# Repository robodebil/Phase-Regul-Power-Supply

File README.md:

# Phase-Regul-Power-Supply
Выпускная Квалификационная работа. Лабораторный блок питания на фазовом управлении

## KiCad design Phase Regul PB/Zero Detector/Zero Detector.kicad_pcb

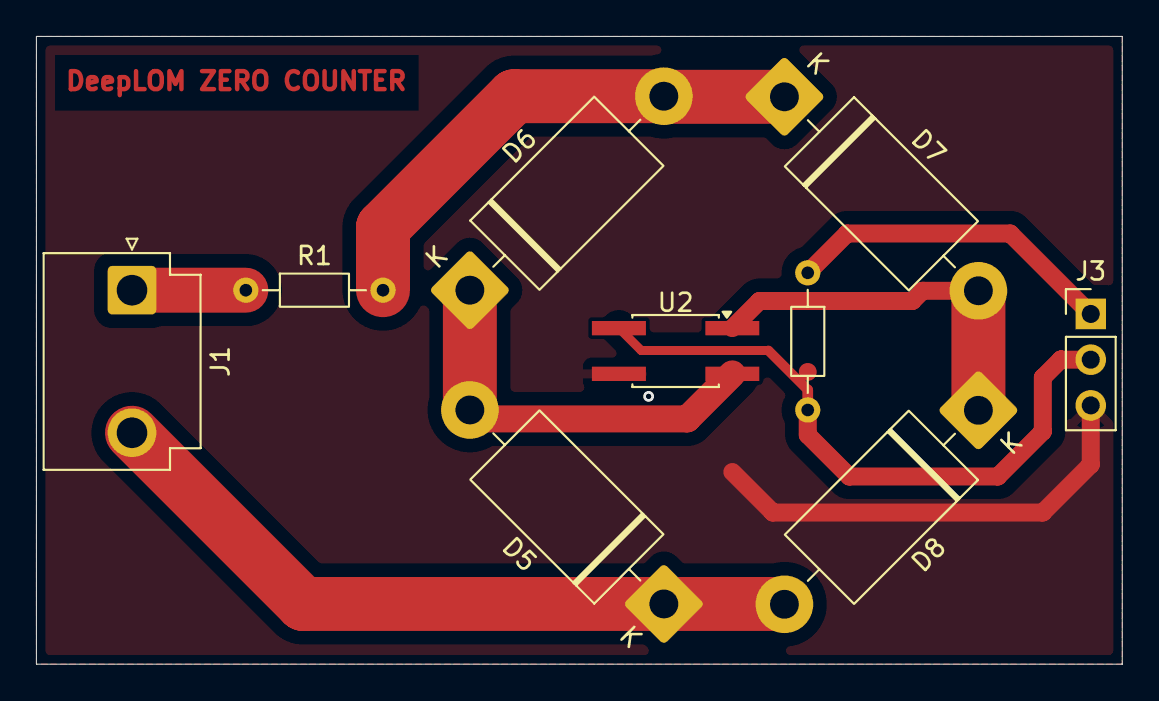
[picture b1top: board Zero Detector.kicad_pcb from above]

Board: 2 copper layers, 60.3 x 34.9 mm, 9 parts (0 on the bottom side), 8 nets.

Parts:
D5, D6, D7, D8: 1N5408; D_DO-201AD_P15.24mm_Horizontal
J1: Conn_01x02; JST_VH_B2P3-VH_1x02_P7.92mm_Vertical
J3: Conn_01x03; PinHeader_1x03_P2.54mm_Vertical
R1: 1M Ohm; R_Axial_DIN0204_L3.6mm_D1.6mm_P7.62mm_Horizontal
R2: 47K Ohm; R_Axial_DIN0204_L3.6mm_D1.6mm_P7.62mm_Horizontal
U2: LTV-357T; SO-4_4.4x3.6mm_P2.54mm

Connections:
/L: J1.1, R1.1
/N: D5.1 (K), D8.2 (A), J1.2
/Zero Detecter: J3.2, R2.2, U2.4
GND: J3.3, U2.3
unnamed: D5.2 (A), D6.1 (K), U2.2
unnamed: D6.2 (A), D7.1 (K), R1.2
unnamed: D7.2 (A), D8.1 (K), U2.1
VCC: J3.1, R2.1

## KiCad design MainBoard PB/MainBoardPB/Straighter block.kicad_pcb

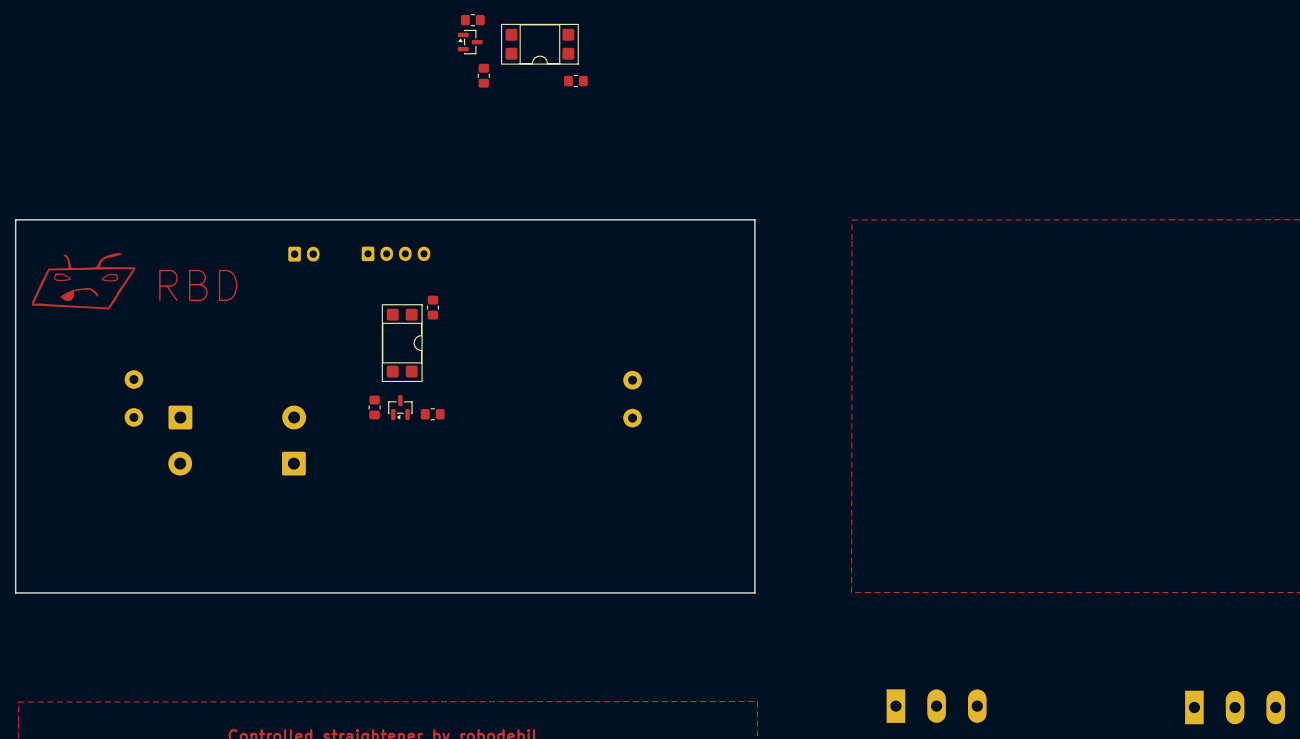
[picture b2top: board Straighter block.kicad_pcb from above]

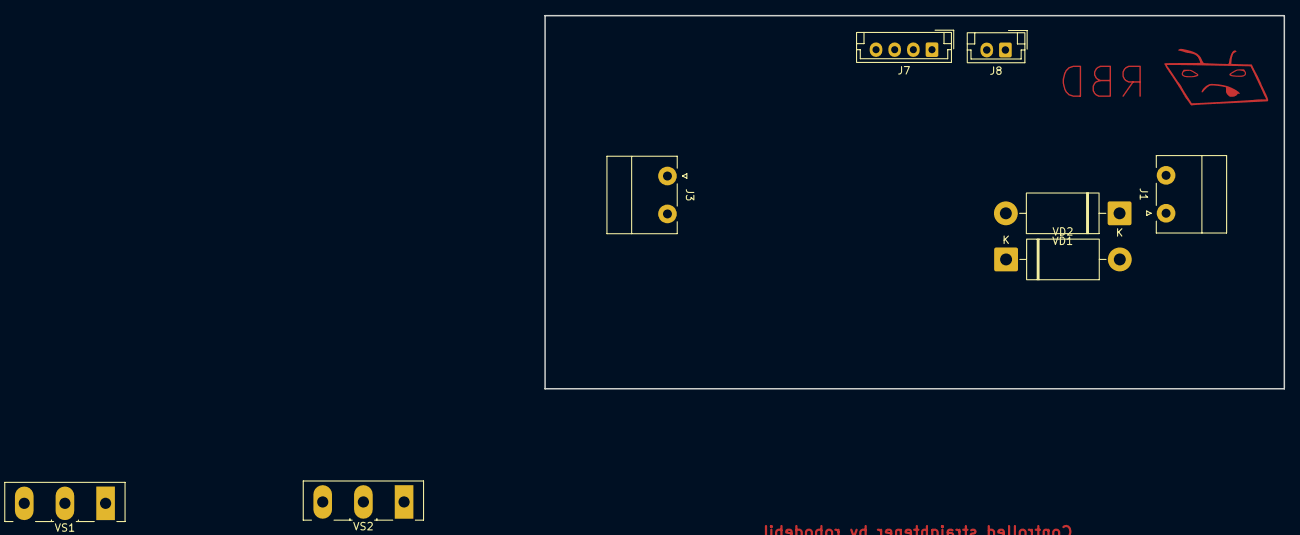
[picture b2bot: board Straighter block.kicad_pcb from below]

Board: 2 copper layers, 99.1 x 50.0 mm, 18 parts (8 on the bottom side), 15 nets, no tracks yet.

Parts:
J1, J3: Conn_01x02; PhoenixContact_MC_1,5_2-G-5.08_1x02_P5.08mm_Horizontal
J7: Conn_01x04; JST_EH_B4B-EH-A_1x04_P2.50mm_Vertical
J8: Conn_01x02; JST_EH_B2B-EH-A_1x02_P2.50mm_Vertical
Q6, Q7: BC817; SOT-23
R7: 1k; R_0805_2012Metric_Pad1.20x1.40mm_HandSolder
R8: 100; R_0805_2012Metric_Pad1.20x1.40mm_HandSolder
R9, R10: 10k; R_0805_2012Metric_Pad1.20x1.40mm_HandSolder
R11, R12: 75; R_0805_2012Metric_Pad1.20x1.40mm_HandSolder
U6, U7: PC817; DIP-4_W7.62mm_SMDSocket_SmallPads
VD1, VD2: 1N5408; D_DO-201AD_P15.24mm_Horizontal
VS1, VS2: VS-40TPS12A-M3; TO-247-3_Vertical

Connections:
+5V: J8.2, Q6.3 (C), Q7.3 (C), U6.4, U7.4
/DC_+: J3.2, VD2.1 (K), VS2.1 (K)
/DC_-: J3.1, VD1.2 (A), VS1.2 (A)
/L: J1.2, VS1.1 (K), VS2.2 (A)
/N: J1.1, VD1.1 (K), VD2.2 (A)
/Tyr1REG: Q6.2 (E), R9.1, R11.2, VS1.3 (G)
/Tyr2REG: Q7.2 (E), R10.1, R12.2, VS2.3 (G)
/Tyr_G1: J7.3, R7.2
/Tyr_G2: J7.2, R8.2
GND: J7.1, U6.2, U7.2
GND1: J8.1, R11.1, R12.1
unnamed: Q6.1 (B), R9.2, U6.3
unnamed: Q7.1 (B), R10.2, U7.3
unnamed: R7.1, U6.1
unnamed: R8.1, U7.1

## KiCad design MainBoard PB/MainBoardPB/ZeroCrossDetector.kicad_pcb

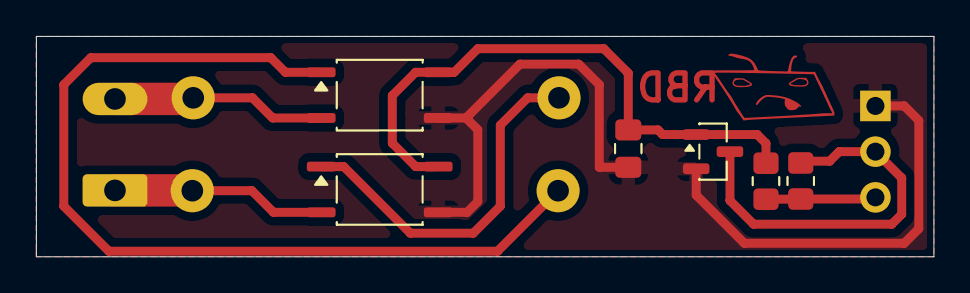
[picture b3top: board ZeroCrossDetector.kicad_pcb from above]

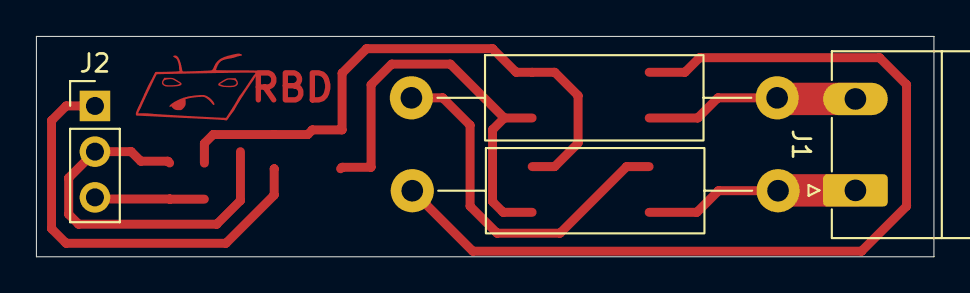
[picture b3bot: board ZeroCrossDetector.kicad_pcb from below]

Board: 2 copper layers, 49.9 x 12.2 mm, 11 parts (4 on the bottom side), 8 nets.

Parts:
C9: 1 nF; C_0805_2012Metric_Pad1.18x1.45mm_HandSolder
J1: Conn_01x02; PhoenixContact_MC_1,5_2-G-5.08_1x02_P5.08mm_Horizontal
J2: Conn_01x03; PinHeader_1x03_P2.54mm_Vertical
Q3: BC847; SOT-23
R13, R14: 150kOhm; R_Axial_DIN0414_L11.9mm_D4.5mm_P20.32mm_Horizontal
R15, R16: 10 kOhm; R_0805_2012Metric_Pad1.20x1.40mm_HandSolder
RBD: LOGO; RBDLogo
U8, U9: TLP181GB-S; SOIC-4_4.55x3.7mm_P2.54mm

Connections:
+3.3V: J2.3, R15.1, R16.2
/L: J1.2, R13.2, U9.3
/N: J1.1, R14.2, U8.3
/Zero_Cross: J2.2, Q3.3 (C), R16.1
GND: C9.2, J2.1, Q3.2 (E), U8.4, U9.4
unnamed: C9.1, Q3.1 (B), R15.2, U8.6, U9.6
unnamed: R13.1, U8.1
unnamed: R14.1, U9.1

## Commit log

2026-05-18 Preddiplom practice
2026-05-18 Добавьте Docs суки
2026-05-18 ДАЙТЕ СУНУТЬ DOCS
2026-05-22 ADD ALL PLEASE DURA EBANAYA
2026-05-26 ПОЛИЛОСЯ ЕПТА БЛЯ
